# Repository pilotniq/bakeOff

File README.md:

# bakeOff
"The missing power button for the Raspberry Pi"
Electronic circuit with On/Off button for Raspberry Pi

These are Eagle schematic and layout files for a circuit that plugs in between the RPi 
micro-USB power jack and the power supply. It has a button that when pressed sends a signal 
to the Raspberry pi to start shutting down safely. When it has shut down, power is cut.

Screw terminals allow you to use your own momentary or regular button. Another pair of screw
terminals let you supply other peripherals with power that is cut at the same time as the Raspberry Pi.
You need to run two wires from the board to the Pi - one for the shutdown signal, and one from Tx to 
sense when the Pi has shut down. There are also two jumpered pins where you can measure the current draw of the Pi.

See the project description on Hackaday: https://hackaday.io/project/9885-raspberry-pi-bake-off

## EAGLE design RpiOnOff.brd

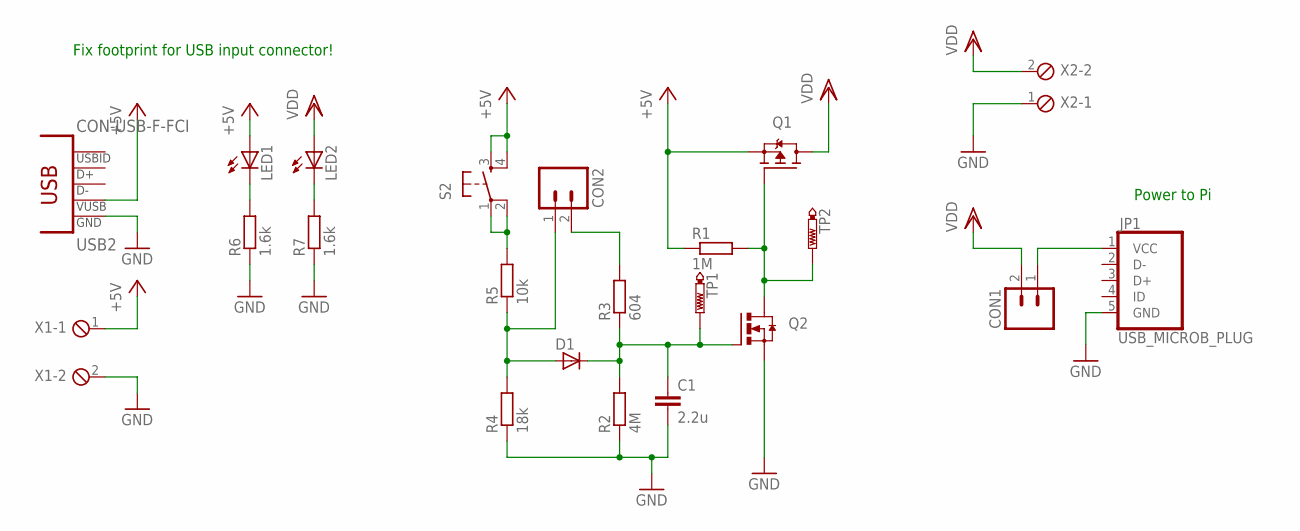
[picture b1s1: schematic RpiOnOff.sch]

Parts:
C1: 2.2u; C0603
CON1, CON2: CONNECTOR-1X2[2.54MM]; CONNECTOR-1X2-2.54MM
D1: D-A1-C3; SOT23
JP1: USB_MICROB_PLUG; CON-USB-MICRO-B-RA-SMT
LED1, LED2: LEDCHIP-LED0603; CHIP-LED0603
Q1: MOSFET-P-TOSHIBA-SSM3J338R; SOT23
Q2: MOSFET-N-SSM3K36MFV; SOT23
R1: 1M; R0603
R2: 4M; R0603
R3: 604; R0603
R4: 18k; R0603
R5: 10k; R0603
R6, R7: 1.6k; R0603
S2: TACT-4PINCK-PTS810; CK-PTS810
TP1, TP2: PTR1B1,27; B1,27
USB2: CON-USB-F-FCI; AMP-USB-MICROB
X1, X2: MPT2; 2POL254

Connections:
+5V: LED1.A, Q1.2 (S), R1.1, S2.3 (S), S2.4 (S1), USB2.1 (VUSB), X1.1
GND: C1.2, JP1.5 (GND), Q2.2 (S), R2.1, R4.1, R6.1, R7.1, USB2.5 (GND), X1.2, X2.1
unnamed: LED1.C, R6.2
unnamed: LED2.C, R7.2
unnamed: CON1.1, JP1.1 (VCC)
unnamed: R5.2, S2.1, S2.2 (P1)
Q1GATE: Q1.1 (G), Q2.3 (D), R1.2, TP2.TP
Q2GATE: C1.1, D1.3 (C), Q2.1 (G), R2.2, R3.1, TP1.TP
SENSE: CON2.1, D1.1 (A), R4.2, R5.1
TX: CON2.2, R3.2
VDD: CON1.2, LED2.A, Q1.3 (D), X2.2

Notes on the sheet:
Power to Pi
Fix footprint for USB input connector!

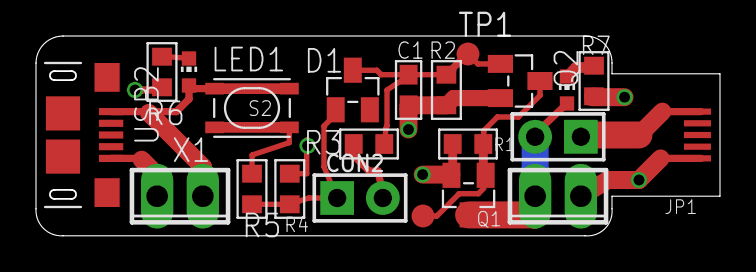
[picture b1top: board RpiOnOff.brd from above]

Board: 2 copper layers, 37.9 x 11.0 mm, 22 parts (0 on the bottom side), 11 nets.

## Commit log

2016-02-26 Initial checkin, ready for PCB order.
2016-03-10 I think the main change was fixing a transistor footprint.
    This is the version that was sent for production to Seeed Studios.
